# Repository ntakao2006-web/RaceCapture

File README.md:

# EcoLogger — 自作の車載データロガー

サーキット走行とエコラン大会で使う、自作の車載データロガーのリポジトリです。
走行中の値（回転数・車速・水温・油温・油圧・G・位置・ラップ）を記録し、車載画面に出し、LTEでピットへ送り、走行映像に計器を焼き込んで録画します。

## いまの姿（2026-11）

| | 中身 | 状態 |
|---|---|---|
| **Ver.2（本番機）** | Arduino UNO Q（Linux＋STM32）＋自作シールド＋UPS基板。車載画面（DASH）、LTE、焼き込み録画つき | 2026-11-08のSUGO 120分耐久を走った形 |
| Ver.1 | ESP32-S3の自作基板。RaceCaptureのアプリにつないで使う | 保険機として据え置き（機能の追加は凍結） |
| カート用 試作0号 | 画面つきの一体型（ESP32-S3） | 2026-11-29の走行に向けて準備中 |

もともとは「RaceCaptureのロガー端末だけを自作のハードウェアに置き換える」計画として始まりました（Ver.1）。
リポジトリ名と`ARCHITECTURE.md`の1〜3章はその頃のままです。

## 読む人ごとの入口

### 使う人（係・ドライバー）

- 当日の手順書（A4で印刷）：[`docs/manual/sugo_day_manual_20261108.html`](docs/manual/sugo_day_manual_20261108.html)（サーキット）、[`docs/manual/ecorun_day_manual_20261024.html`](docs/manual/ecorun_day_manual_20261024.html)（エコラン）
- 困ったとき：[`docs/manual/ecologger_troubleshooting.html`](docs/manual/ecologger_troubleshooting.html)
- PCの操作メニュー：`tools/ecologger_menu/`（デスクトップの「EcoLogger Ver.2」）
- 走行ログ・動画の回収：`tools/video_collect/Collect-Video.cmd`

### チーム

- ハードウェアとソフトウェアの構成図：[`v2_hardware_overview.html`](v2_hardware_overview.html)
- 仕様書（誰に・どの場面で・何をできるようにするか）：[`SPEC.md`](SPEC.md)

### 開発者

- **[`ARCHITECTURE.md`](ARCHITECTURE.md)** — 現在地とロードマップ（このリポジトリの一次情報源）
- 作業の分解：直下の`task_*_breakdown.md`（一覧は`ARCHITECTURE.md` 5章の冒頭「タスクの置き場所」）
- 資料1本ごとの案内：[`docs/README.md`](docs/README.md)、道具ごとの案内：[`tools/README.md`](tools/README.md)
- 各フォルダーの`README.md`

## フォルダー

| 場所 | 中身 |
|---|---|
| `RaceCapture-UNOQ/` | Ver.2のLinux側（車載画面DASH・見守り役など） |
| `EcoCapture-Web/` | Ver.2の上で動くEcoCapture（設定・ログ管理・LTE送信） |
| `tools/` | PCで使う道具（操作メニュー・回収・解析・動画）と、本体の録画のソフト`tools/unoq_overlay_enc/` |
| `tools/dev/` | 開発・調べもの用の道具 |
| `firmware/` | Ver.1のファームウェア（PlatformIO / ESP-IDF） |
| `android-logger/` | スマホのアプリ（エコランの車載画面） |
| `circuit/` | 回路・基板（KiCad） |
| `docs/design/` | 仕様・設計 |
| `docs/manual/` | 手順書 |
| `docs/research/` | 調査 |
| `docs/share/` | 人に渡したメモと、その回答 |
| `ecorun/` | エコランチームの用事（記録表） |
| `outputs/` | 確かめの記録（日付つき） |
| `archive/` | 閉じた系統の資料（ダッシュカム・通話など） |

走行ログ（`drive_logs/`）は位置情報を含むため、リポジトリには入れていません。

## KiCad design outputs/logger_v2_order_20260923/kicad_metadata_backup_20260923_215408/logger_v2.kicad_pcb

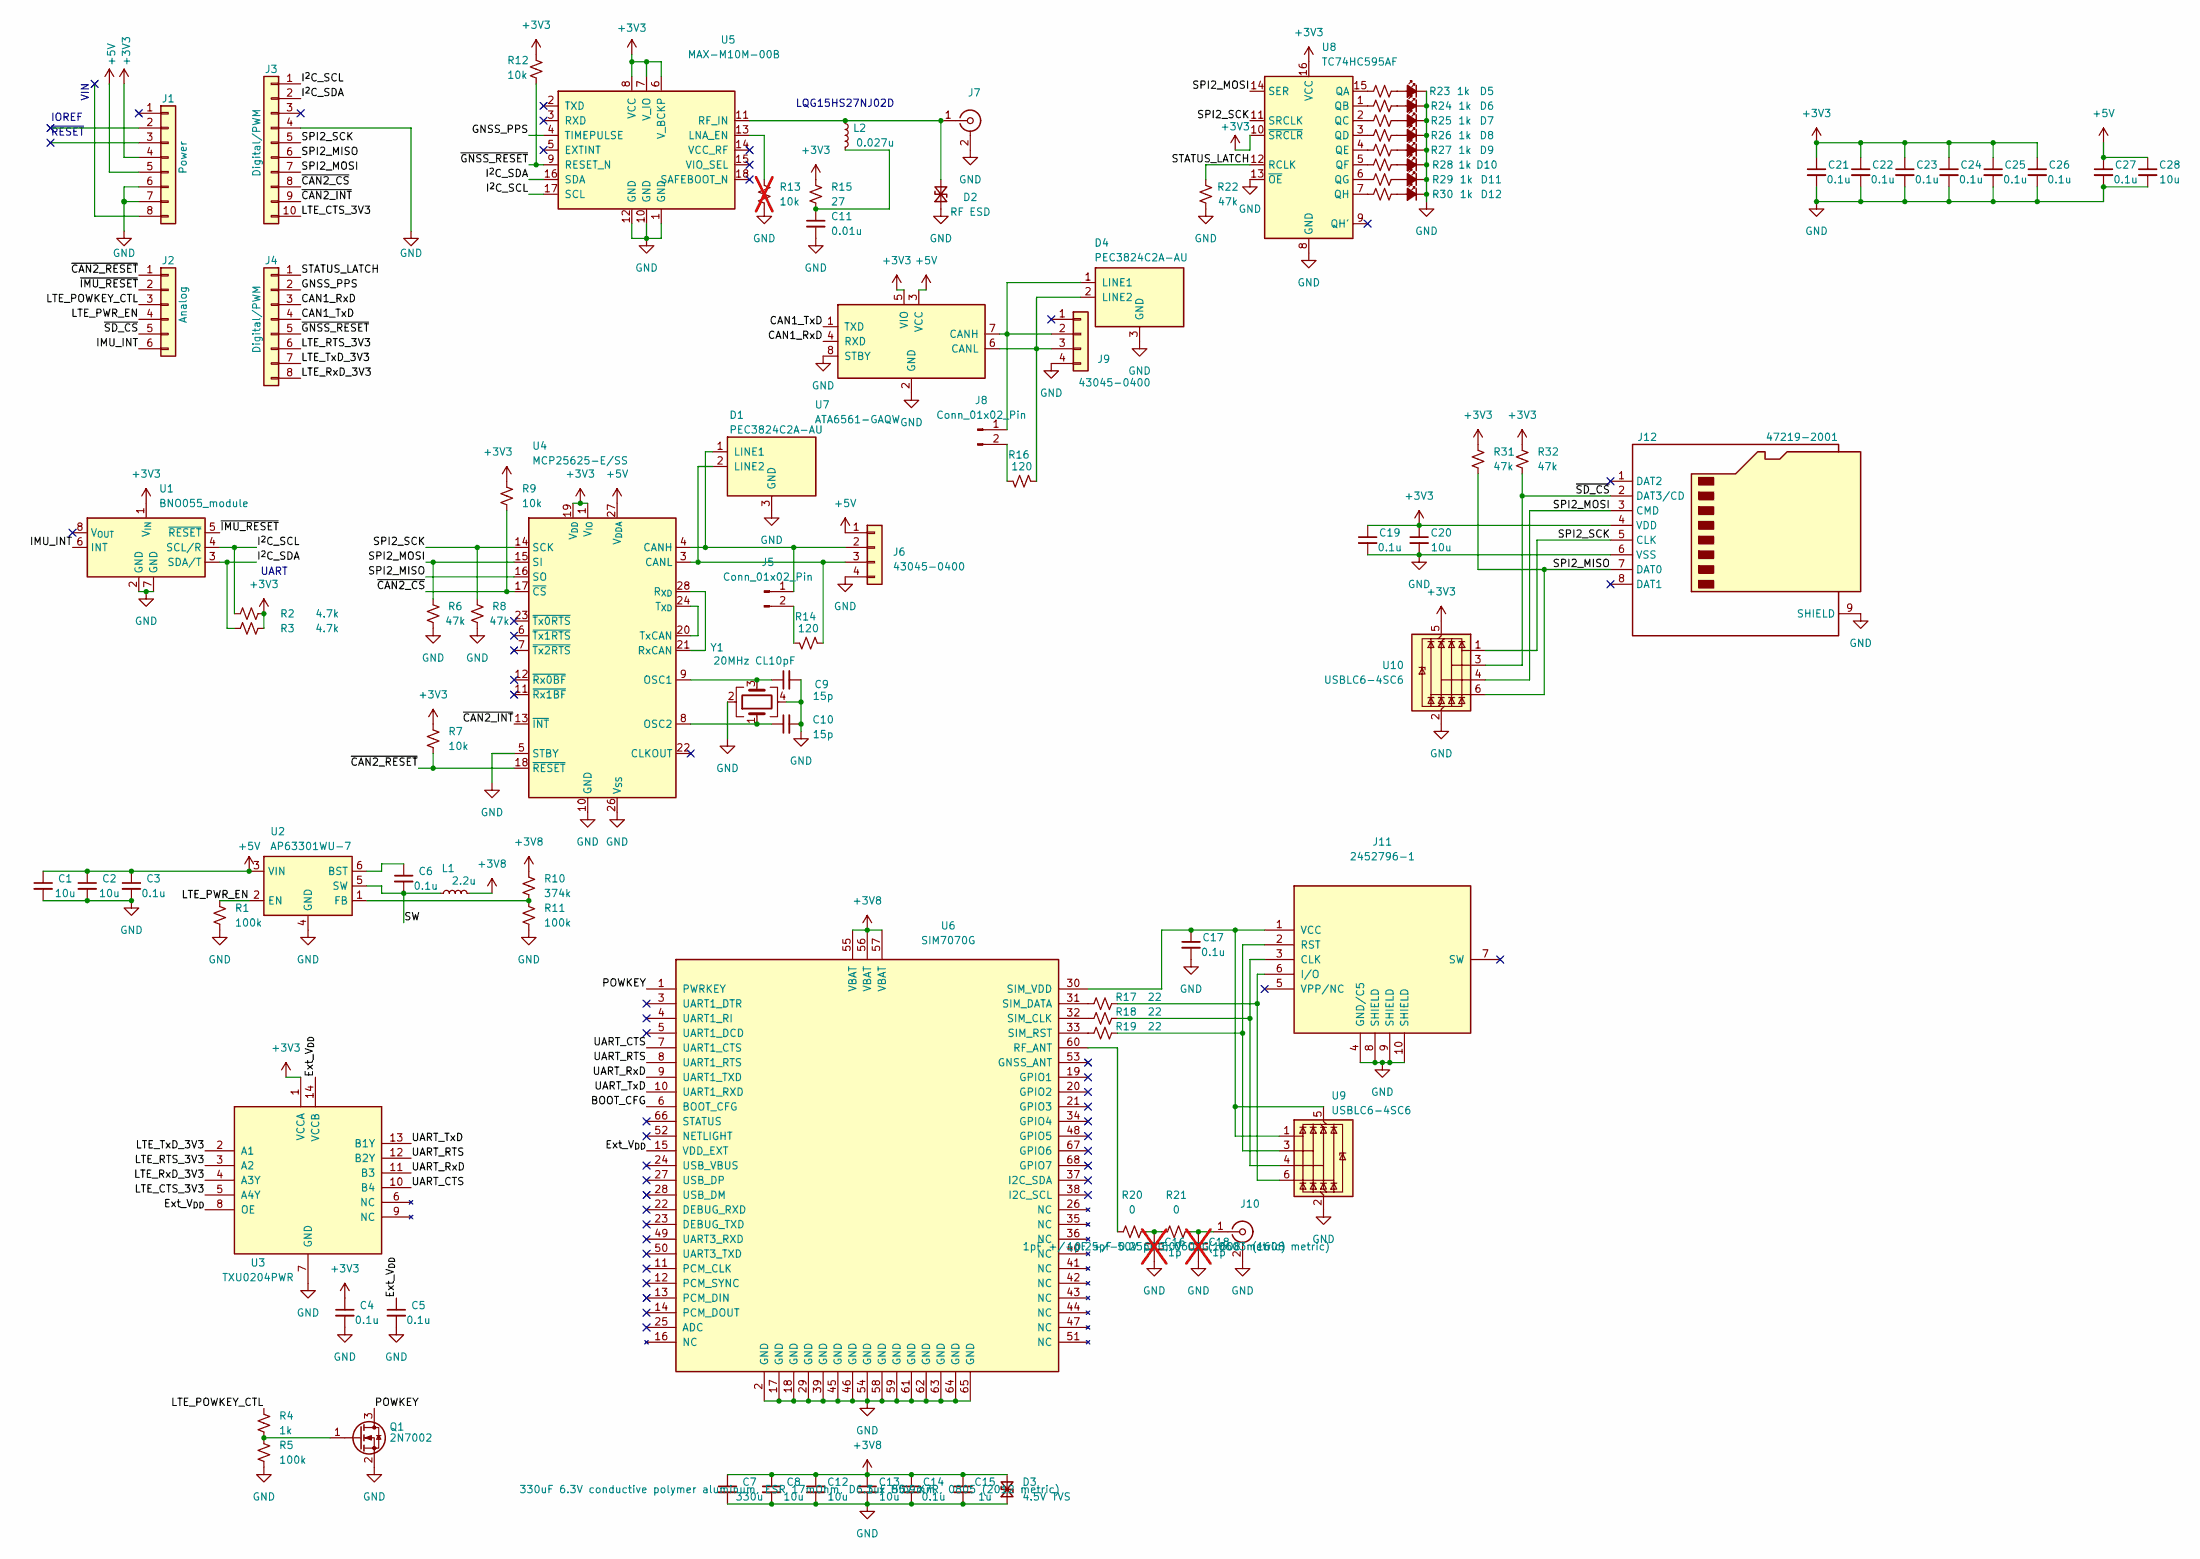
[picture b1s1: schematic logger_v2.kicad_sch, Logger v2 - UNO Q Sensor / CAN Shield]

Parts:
C1, C2, C8, C12, C13, C28: 10u; C_0805_2012Metric; MPN GRM21BR71A106KE51; LCSC C15850
C3, C4, C5, C6, C14, C17, C19, C21, C22, C23, C24, C25, C26, C27: 0.1u; C_0603_1608Metric; MPN GRM188R72A104KA35D; LCSC C14663
C7: 330u; CP_Elec_6.3x5.9; MPN 6SVPC330M
C9, C10: 15p; C_0603_1608Metric; MPN CC0603N150J500; LCSC C1647
C11: 0.01u; C_0603_1608Metric; MPN GRM188B11H103KA01; LCSC C14663
C15: 1u; C_0805_2012Metric; MPN C2012X7R1H105KT000N
C16, C18: 1p; C_0603_1608Metric; MPN CC0603CRNPO9BN1R0; not fitted
C20: 10u; C_0805_2012Metric; MPN C2012X7R1H105KT000N
D1, D4: PEC3824C2A-AU; SOT-23; MPN PEC3824C2A-AU_R1_000A1; LCSC C14486
D2: RF ESD; D_SOD-882; MPN PESD5V0F1BL-Q; LCSC C45961
D3: 4.5V TVS; Prisemi_DFN1006_2L
D5, D6, D7, D8, D9, D10, D11, D12: GREEN 0805; LED_0805_2012Metric_ShieldSilk; MPN OSG80805C1C; LCSC C2297
J1: Power; PinHeader_1x08_P2.54mm_Vertical; MPN FH105-1x8SG/RH
J2: Analog; PinHeader_1x06_P2.54mm_Vertical; MPN FH105-1x6SG/RH
J3: Digital/PWM; PinHeader_1x10_P2.54mm_Vertical; MPN FH105-1x10SG
J4: Digital/PWM; PinHeader_1x08_P2.54mm_Vertical; MPN FH105-1x8SG/RH
J5, J8: Conn_01x02_Pin; PinHeader_1x02_P2.54mm_Vertical
J6, J9: 43045-0400; Molex_Micro-Fit_3.0_43045-0400_2x02_P3.00mm_Horizontal; MPN 43045-0400
J7, J10: S-037-TGG; SMA_S-037-TGG_Horizontal; MPN S-037-TGG
J11: 2452796-1; nanoSIM_TE_2452796-1_Hinge; MPN 2452796-1
J12: 47219-2001; Molex_47219-2001; MPN 47219-2001
L1: 2.2u; L_Murata_DFE252012P; MPN DFE252012P-2R2M=P2
L2: 0.027u; L_0603_1608Metric; MPN LQW18AN27NJ00D
Q1: 2N7002; SOT-23; MPN 2N7002
R1, R5, R11: 100k; R_0603_1608Metric; MPN RK73B1JTTD103J; LCSC C25804
R2, R3: 4.7k; R_0603_1608Metric; MPN RK73B1JTTD472J; LCSC C23162
R4: 1k; R_0603_1608Metric; MPN RK73B1JTTD103J; LCSC C25804
R6, R8, R22: 47k; R_0603_1608Metric; MPN RC0603J47K; LCSC C25819
R7, R9, R12: 10k; R_0603_1608Metric; MPN RK73B1JTTD103J; LCSC C25804
R10: 374k; R_0603_1608Metric; MPN RK73B1JTTD103J; LCSC C25804
R13: 10k; R_0603_1608Metric; MPN RK73B1JTTD103J; LCSC C25804; not fitted
R14, R16: 120; R_0603_1608Metric; MPN RC0603J120R; LCSC C22787
R15: 27; R_2512_6332Metric; MPN CRCW251227R0JNEG; LCSC C25478
R17, R18, R19: 22; R_0603_1608Metric; MPN RK73B1JTTD103J; LCSC C25804
R20, R21: 0; R_0603_1608Metric; MPN RK73B1JTTD103J; LCSC C25804
R23, R24, R25, R26, R27, R28, R29, R30: 1k; R_0603_1608Metric; MPN RK73B1JTTD102J; LCSC C23228
R31, R32: 47k; R_0603_1608Metric; MPN RK73B1JTTD103J; LCSC C25804
U1: BNO055_module; AE_BNO055_BO_ShieldSilk; MPN AE-BNO055-BO
U2: AP63301WU-7; Diodes_TSOT26; MPN AP63301WU-7
U3: TXU0204PWR; TSSOP-14_4.4x5mm_P0.65mm; MPN TXU0204PWR
U4: MCP25625-E/SS; SSOP-28_5.3x10.2mm_P0.65mm; MPN MCP25625T-E/SS; LCSC C184944
U5: MAX-M10M-00B; MAX_M10M_00B_LCC18; MPN MAX-M10M-00B; LCSC C5119087
U6: SIM7070G; SIMCom_SIM7070G_LCC68_24x24mm_P1mm; MPN SIM7070G
U7: ATA6561-GAQW; SOIC-8_3.9x4.9mm_P1.27mm; MPN ATA6561-GAQW-N; LCSC C2929602
U8: TC74HC595AF; Toshiba_SOP16_P300_1.27A; MPN TC74HC595AF; LCSC C5947
U9, U10: USBLC6-4SC6; SOT-23-6; MPN USBLC6-4SC6
Y1: 20MHz CL10pF; Crystal_SMD_3225-4Pin_3.2x2.5mm; MPN 20M10PB/XT324-10/80; LCSC C18213008

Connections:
+3V3: C4.1, C19.1, C20.1, C21.1, C22.1, C23.1, C24.1, C25.1, C26.1, J1.4, J12.4 (VDD), R2.2, R3.2, R7.1, R9.1, R12.1, R15.1, R31.1, R32.1, U1.1 (V_{IN}), U3.1 (VCCA), U4.1 (V_{IO}), U4.19 (V_{DD}), U5.6 (V_BCKP), U5.7 (V_IO), U5.8 (VCC), U7.5 (VIO), U8.10 (~SRCLR), U8.16 (VCC), U10.5 (VBUS)
+3V8: C7.1, C8.1, C12.1, C13.1, C14.1, C15.1, D3.2 (A2), L1.2, R10.1, U6.55 (VBAT), U6.56 (VBAT), U6.57 (VBAT)
+5V: C1.1, C2.1, C3.1, C27.1, C28.1, J1.5, J6.1, U2.3 (VIN), U4.27 (V_{DDA}), U7.3 (VCC)
/BOOT_CFG: U6.6 (BOOT_CFG)
/CAN1_RxD: J4.3, U7.4 (RXD)
/CAN1_TxD: J4.4, U7.1 (TXD)
/Ext_V_{DD}: C5.1, U3.8 (OE), U3.14 (VCCB), U6.15 (VDD_EXT)
/GNSS_PPS: J4.2, U5.4 (TIMEPULSE)
/IMU_INT: J2.6, U1.6 (INT)
/I^{2}C_SCL: J3.1, R2.1, U1.4 (SCL/R), U5.17 (SCL)
/I^{2}C_SDA: J3.2, R3.1, U1.3 (SDA/T), U5.16 (SDA)
/LTE_CTS_3V3: J3.10, U3.5 (A4Y)
/LTE_POWKEY_CTL: J2.3, R4.1
/LTE_PWR_EN: J2.4, R1.1, U2.2 (EN)
/LTE_RTS_3V3: J4.6, U3.3 (A2)
/LTE_RxD_3V3: J4.8, U3.4 (A3Y)
/LTE_TxD_3V3: J4.7, U3.2 (A1)
/POWKEY: Q1.3 (D), U6.1 (PWRKEY)
/SPI2_MISO: J3.6, J12.7 (DAT0), R31.2, U4.16 (SO), U10.6 (I/O4)
/SPI2_MOSI: J3.7, J12.3 (CMD), R6.1, U4.15 (SI), U8.14 (SER), U10.4 (I/O3)
/SPI2_SCK: J3.5, J12.5 (CLK), R8.1, U4.14 (SCK), U8.11 (SRCLK), U10.1 (I/O1)
/STATUS_LATCH: J4.1, R22.1, U8.12 (RCLK)
/SW: C6.2, L1.1, U2.5 (SW)
/UART_CTS: U3.10 (B4), U6.7 (UART1_CTS)
/UART_RTS: U3.12 (B2Y), U6.8 (UART1_RTS)
/UART_RxD: U3.11 (B3), U6.9 (UART1_TXD)
/UART_TxD: U3.13 (B1Y), U6.10 (UART1_RXD)
/~CAN2_CS: J3.8, R9.2, U4.17 (~CS)
/~CAN2_INT: J3.9, U4.13 (~INT)
/~CAN2_RESET: J2.1, R7.2, U4.18 (~RESET)
/~GNSS_RESET: J4.5, R12.2, U5.9 (RESET_N)
/~IMU_RESET: J2.2, U1.5 (~RESET)
/~SD_CS: J2.5, J12.2 (DAT3/CD), R32.2, U10.3 (I/O2)
GND: C1.2, C2.2, C3.2, C4.2, C5.2, C7.2, C8.2, C9.2, C10.2, C11.2, C12.2, C13.2, C14.2, C15.2, C16.2, C17.2, C18.2, C19.2, C20.2, C21.2, C22.2, C23.2, C24.2, C25.2, C26.2, C27.2, C28.2, D1.3 (GND), D2.1 (A1), D3.1 (A1), D4.3 (GND), D5.1 (K), D6.1 (K), D7.1 (K), D8.1 (K), D9.1 (K), D10.1 (K), D11.1 (K), D12.1 (K), J1.6, J1.7, J3.4, J6.4, J7.2 (Ext), J9.4, J10.2 (Ext), J11.4 (GND/C5), J11.8 (SHIELD), J11.9 (SHIELD), J11.10 (SHIELD), J12.6 (VSS), J12.9 (SHIELD), Q1.2 (S), R1.2, R5.2, R6.2, R8.2, R11.2, R13.2, R22.2, U1.2 (GND), U1.7 (GND), U2.4 (GND), U3.7 (GND), U4.5 (STBY), U4.10 (GND), U4.26 (V_{SS}), U5.1 (GND), U5.10 (GND), U5.12 (GND), U6.2 (GND), U6.17 (GND), U6.18 (GND), U6.29 (GND), U6.39 (GND), U6.45 (GND), U6.46 (GND), U6.54 (GND), U6.58 (GND), U6.59 (GND)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
unnamed: C11.1, L2.2, R15.2
unnamed: C16.1, R20.2, R21.1
unnamed: D1.1 (LINE1), J5.1, J6.2, U4.4 (CANH)
unnamed: D1.2 (LINE2), J6.3, R14.1, U4.3 (CANL)
unnamed: D2.2 (A2), J7.1 (In), L2.1, U5.11 (RF_IN)
unnamed: D4.1 (LINE1), J8.1, J9.2, U7.7 (CANH)
unnamed: D4.2 (LINE2), J9.3, R16.1, U7.6 (CANL)
unnamed: D5.2 (A), R23.2
unnamed: D6.2 (A), R24.2
unnamed: D7.2 (A), R25.2
unnamed: D8.2 (A), R26.2
unnamed: D9.2 (A), R27.2
unnamed: D10.2 (A), R28.2
unnamed: D11.2 (A), R29.2
unnamed: D12.2 (A), R30.2
unnamed: J5.2, R14.2
unnamed: J8.2, R16.2
unnamed: C18.1, J10.1 (In), R21.2
unnamed: J11.3 (CLK), R18.2, U9.4 (I/O3)
unnamed: J11.6 (I/O), R17.2, U9.6 (I/O4)
unnamed: J11.2 (RST), R19.2, U9.3 (I/O2)
unnamed: C17.1, J11.1 (VCC), U6.30 (SIM_VDD), U9.1 (I/O1), U9.5 (VBUS)
unnamed: Q1.1 (G), R4.2, R5.1
unnamed: C6.1, U2.6 (BST)
unnamed: R10.2, R11.1, U2.1 (FB)
unnamed: C9.1, U4.9 (OSC1), Y1.3
unnamed: C10.1, U4.8 (OSC2), Y1.1
unnamed: U4.21 (RxCAN), U4.28 (R_{XD})
unnamed: U4.20 (TxCAN), U4.24 (T_{XD})
unnamed: R13.1, U5.13 (LNA_EN)
unnamed: R20.1, U6.60 (RF_ANT)
unnamed: R18.1, U6.32 (SIM_CLK)
unnamed: R17.1, U6.31 (SIM_DATA)
unnamed: R19.1, U6.33 (SIM_RST)
unnamed: R23.1, U8.15 (QA)
unnamed: R24.1, U8.1 (QB)
unnamed: R25.1, U8.2 (QC)
unnamed: R26.1, U8.3 (QD)
unnamed: R27.1, U8.4 (QE)
unnamed: R28.1, U8.5 (QF)
unnamed: R29.1, U8.6 (QG)
unnamed: R30.1, U8.7 (QH)

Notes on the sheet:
UART
~{RESET}
LQG15HS27NJ02D
VIN
IOREF

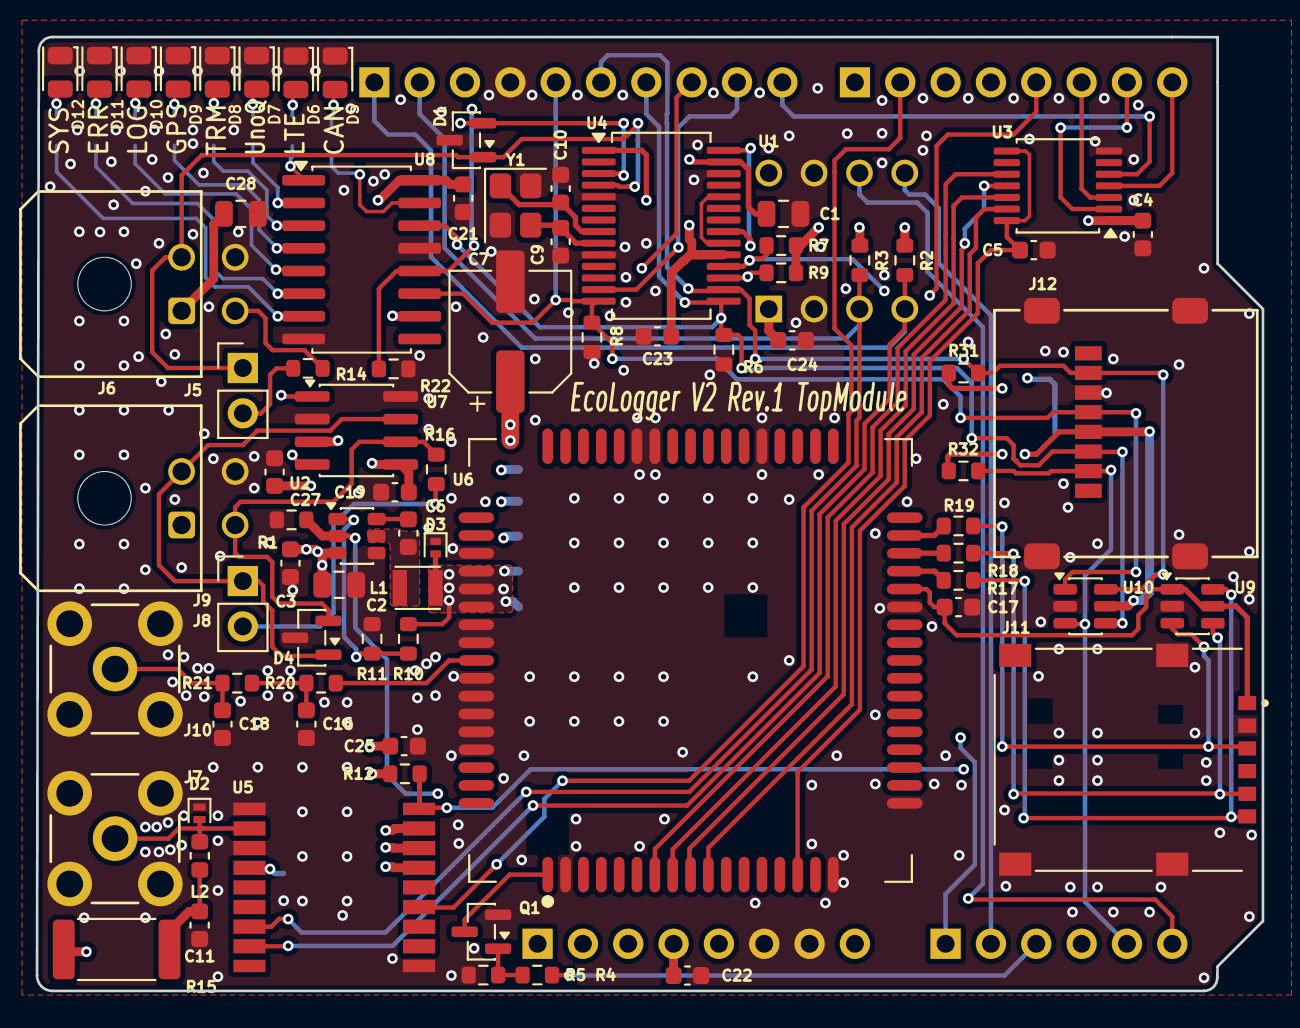
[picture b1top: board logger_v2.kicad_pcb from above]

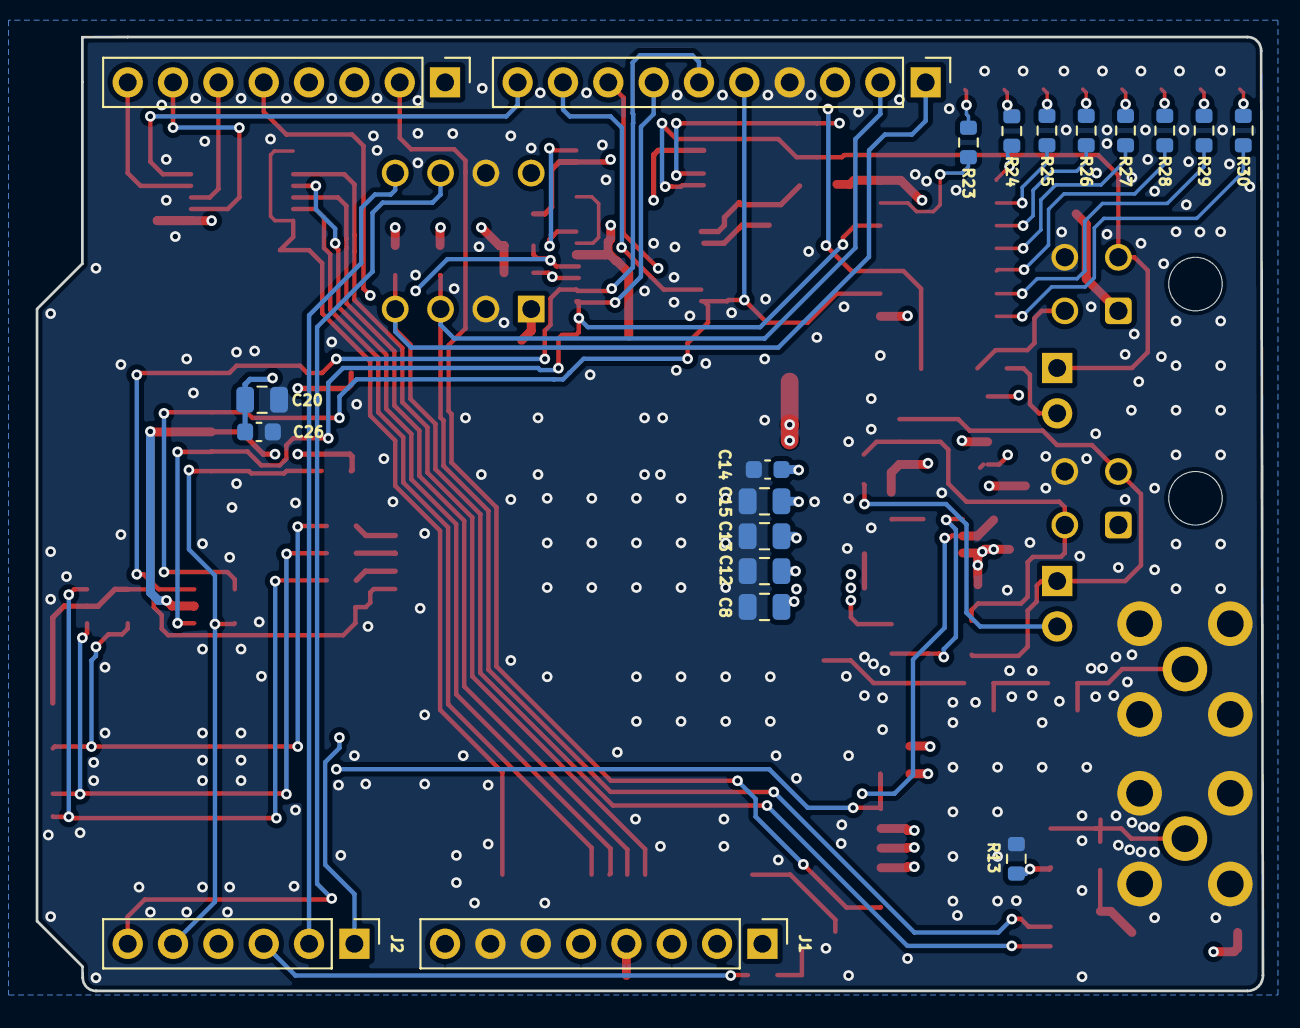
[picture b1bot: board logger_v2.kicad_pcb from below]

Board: 4 copper layers, 68.7 x 53.4 mm, 98 parts (20 on the bottom side), 75 nets.

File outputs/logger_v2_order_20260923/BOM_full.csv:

"状態","実装位置","品目","サイズ","メーカー品番","販売店","販売店品番","必要数","予備候補数","購入推奨数","選定根拠","製品URL"
"在庫表示あり","C1 C2 C8 C12 C13 C20 C28","10µF ±10% X7R 10V","0805 / 2012","CL21B106KPQNFNE","DigiKey","1276-2934-1-ND","7","3","10","旧445-6857-1-NDが注文画面で入荷待ちのため差替え。Samsung製10µF±10%・10V・X7R、2.00×1.25mm、高さ最大1.40mm。同じ0805ランドに実装可能。DigiKey製品ページの直販在庫65,218個、CT10個284円（税別）表示を2026-09-23確認。実装7＋予備3。C20は現行Value=10u。","https://www.digikey.jp/en/products/detail/samsung-electro-me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"
"在庫表示あり","C3 C4 C5 C6 C14 C17 C19 C21 C22 C23 C24 C25 C26 C27","100nF ±10% X7R 100V","0603 / 1608","GRM188R72A104KA35D","DigiKey","490-3285-1-ND","14","11","25","現行MPNを維持。C21～C27も現行Value=0.1u。","https://www.digikey.jp/en/products/detail/murata-electronics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"
"在庫表示あり","C7","330µF 6.3V ポリマー","φ6.3 × H5.9mm","6SVPC330M","DigiKey","P16611CT-ND","1","1","2","指定品維持。ESR17mΩ、極性あり。","https://www.digikey.jp/en/products/detail/panasonic-industry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"
"在庫表示あり","C9 C10","15pF ±5% C0G 50V","0603 / 1608","CC0603JRNPO9BN150","DigiKey","311-1060-1-ND","2","8","10","Value=15pを採用。古いSpecificationの18pF/CL12pFは不採用。 少量価格の段差も考慮して10個。","https://www.digikey.jp/en/products/detail/yageo/CC0603JRNPO9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"
"在庫表示あり","C11","10nF ±10% X7R 100V","0603 / 1608","GRM188R72A103KA01D","DigiKey","490-GRM188R72A103KA01DCT-ND","1","9","10","現行Value=0.01u。耐圧は元の50V以上。 少量価格の段差も考慮して10個。","https://www.digikey.jp/en/products/detail/murata-electronics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"
"在庫表示あり","C15","1µF ±10% X7R 50V","0805 / 2012","C2012X7R1H105K085AC","DigiKey","445-14539-1-ND","1","2","3","同サイズ・同容量・同耐圧。高さ最大1.0mm。新規設計非推奨品だが在庫表示あり。","https://www.digikey.jp/en/products/detail/tdk-corporation/C2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"
"在庫表示あり","D1 D4","CAN用 双方向2線 TVS 24V","SOT-23-3","ESDCAN24-2BLY","DigiKey","497-13262-1-ND","2","2","4","PEC3824C2A-AUの代替。1/2=CAN、3=GND。24V、Vbr最低27V、容量最大30pF。クランプ特性は元品と完全同一ではない。","https://www.digikey.jp/en/products/detail/stmicroelectronics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"
"在庫表示あり","D5 D6 D7 D8 D9 D10 D11 D12","緑LED 571nm / Vf約2V","0805 / 2012","LTST-C170KGKT","DigiKey","160-1414-1-ND","8","4","12","同0805、1=カソード、2=アノード。元品と発光色・明るさに差あり。","https://www.digikey.jp/en/products/detail/liteon/LTST-C170KG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"
"在庫表示あり","J6 J9","Micro-Fit 3.0 基板側4極","2×2 / 3.0mm 横向きTHT","43045-0400","DigiKey","WM1814-ND","2","0","2","43045-0400と同じ品番の表記違い。指定どおり2個だけ。ケーブル側・圧着端子は含めない。","https://www.digikey.jp/en/products/detail/molex/0430450400/252527"
"在庫表示あり","J11","nanoSIM ヒンジ式ソケット","TE専用フットプリント","2452796-1","DigiKey","343-2452796-1CT-ND","1","1","2","SDとは別部品。現行指定品維持。マーケットプレイス品ではなくDigiKey直販CTを指定。","https://www.digikey.jp/en/products/detail/te-connectivity-li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"
"在庫表示あり","L1","2.2µH ±20% 電源インダクタ","2.5×2.0×1.2mm","DFE252012F-2R2M=P2","DigiKey","490-13055-1-ND","1","2","3","旧490-10649-1-NDがユーザーのカートで規制表示のためFシリーズへ差替え。2.2µH±20%、外形・高さ・推奨ランド（内側1.2/外側2.8/幅2.0mm）は元品と一致。Irms2.3A / Isat3.3A / DCR82mΩ最大（元2.2A/3.0A/84mΩ）。DigiKey直販190,191個、1個税別42円の表示を2026-09-23確認。3個＝実装1＋予備2。ユーザーカートでの規制解除は未確認。","https://www.digikey.jp/en/products/detail/murata-electronics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"
"在庫表示あり","L2","27nH RF巻線インダクタ","0603 / 1608","LQW18AN27NJ00D","DigiKey","490-1174-1-ND","1","2","3","指定品維持。440mA、SRF3.7GHz以上。一般電源用インダクタには置換しない。","https://www.digikey.jp/en/products/detail/murata-electronics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"
"在庫表示あり","Q1","Nch MOSFET 60V","SOT-23","2N7002ET1G","DigiKey","2N7002ET1GOSCT-ND","1","2","3","2N7002相当。1=G、2=S、3=Dで基板と一致。","https://www.digikey.jp/en/products/detail/onsemi/2N7002ET1G/1792136"
"在庫表示あり","R1 R5 R11","100kΩ ±0.1% 0.1W","0603 / 1608","CRT0603-BY-1003ELF","DigiKey","CRT0603-BY-1003ELFCT-ND","3","7","10","0603・100kΩ・0.1%・0.1W。R11の帰還精度を優先し同一品へ統一。","https://www.digikey.jp/en/products/detail/bourns-inc/CRT0603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"
"在庫表示あり","R4 R23 R24 R25 R26 R27 R28 R29 R30","1kΩ ±1% 0.1W","0603 / 1608","RC0603FR-071KL","DigiKey","311-1.00KHRCT-ND","9","6","15","Value基準。古いMPNに10kΩ表記が残る箇所あり。","https://www.digikey.jp/en/products/detail/yageo/RC0603FR-071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"
"在庫表示あり","R6 R8 R22 R31 R32","47kΩ ±1% 0.1W","0603 / 1608","RC0603FR-0747KL","DigiKey","311-47.0KHRCT-ND","5","5","10","同サイズの1%品。","https://www.digikey.jp/en/products/detail/yageo/RC0603FR-074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"
"在庫表示あり","R10","374kΩ ±1% 0.1W","0603 / 1608","RC0603FR-07374KL","DigiKey","311-374KHRCT-ND","1","9","10","電源帰還上側。Value=374kを採用。 少量価格の段差も考慮して10個。","https://www.digikey.jp/en/products/detail/yageo/RC0603FR-073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"
"在庫表示あり","R14 R16","120Ω ±1% 0.1W","0603 / 1608","RC0603FR-07120RL","DigiKey","311-120HRCT-ND","2","8","10","現行DNP=noのため含む。接続するCANバスの終端配置に従って実装する。 少量価格の段差も考慮して10個。","https://www.digikey.jp/en/products/detail/yageo/RC0603FR-071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"
"在庫表示あり","R17 R18 R19","22Ω ±1% 0.1W","0603 / 1608","CRCW060322R0FKEA","DigiKey","541-22.0HCT-ND","3","7","10","0603・22Ω・1%・0.1Wを維持。在庫表示のあるVishay品。","https://www.digikey.jp/en/products/detail/vishay-dale/CRCW06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"
"在庫表示あり","R20 R21","0Ω ジャンパ 0.1W","0603 / 1608","RC0603JR-070RL","DigiKey","311-0.0GRCT-ND","2","8","10","現行Value=0Ω。 少量価格の段差も考慮して10個。","https://www.digikey.jp/en/products/detail/yageo/RC0603JR-070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"
"在庫表示あり","R15","27Ω ±5% 1W","2512 / 6332","RMCF2512JT27R0","DigiKey","RMCF2512JT27R0CT-ND","1","2","3","2512・27Ω・5%・1Wを維持。同サイズのStackpole品へ置換。","https://www.digikey.jp/en/products/detail/stackpole-electron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"
"在庫表示あり","U2","3A 降圧DC/DC","TSOT26","AP63301WU-7","DigiKey","31-AP63301WU-7CT-ND","1","1","2","指定品維持。AP63300/固定電圧版と混同しない。","https://www.digikey.jp/en/products/detail/diodes-incorporate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"
"在庫表示あり","U3","4bit レベル変換","TSSOP-14 / P0.65","TXU0204PWR","DigiKey","296-TXU0204PWRCT-ND","1","1","2","指定品維持。PWパッケージ。","https://www.digikey.jp/en/products/detail/texas-instruments/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"
"在庫表示あり","U4","CANコントローラ＋トランシーバ","SSOP-28 / 幅5.3mm","MCP25625T-E/SS","DigiKey","MCP25625T-E/SSCT-ND","1","0","1","指定品維持。/SSパッケージ。高価なため予備なし。","https://www.digikey.jp/en/products/detail/microchip-technolo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"
"在庫表示あり","U6","LTE Cat-M/NB-IoTモジュール","LCC-68 / 24×24mm","SIM7070G","DigiKey","3781-SIM7070G-ND","1","0","1","指定の裸モジュール。開発ボードではない。高価なため予備なし。","https://www.digikey.jp/en/products/detail/simcom-wireless-so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"
"在庫表示あり","U7","CANトランシーバ","SOIC-8 / 幅3.9mm","ATA6561-GAQW-N","DigiKey","ATA6561-GAQW-NCT-ND","1","1","2","指定品維持。VDFN版を選ばない。","https://www.digikey.jp/en/products/detail/microchip-technolo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"
"在庫表示あり","U8","8bit シフトレジスタ","SOP-16 / 幅5.3mm","TC74HC595AF(EL,F)","DigiKey","264-TC74HC595AF(EL,F)CT-ND","1","1","2","指定AFのSOP16を維持。一般的な幅3.9mm SOICの74HC595は合わない。","https://www.digikey.jp/en/products/detail/toshiba-semiconduc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"
"在庫表示あり","U9 U10","4線ESD保護","SOT-23-6","USBLC6-4SC6Y","DigiKey","497-11883-1-ND","2","2","4","USBLC6-4SC6の車載グレード品。同じ4線・SOT23-6・ピン配置。2=GND、5=VBUS、1/3/4/6=I/O。","https://www.digikey.jp/en/products/detail/stmicroelectronics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"
"在庫表示あり","Y1","水晶 20MHz / CL10pF","3225 / 4端子","ABM8-20.000MHZ-10-B1U-T","DigiKey","535-14973-1-ND","1","1","2","同寸法3.2×2.5mm、CL10pF。1/3=水晶、2/4=GND。発振余裕は実機で確認。","https://www.digikey.jp/en/products/detail/abracon-llc/ABM8-2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"
"在庫表示あり：機能代替","D2","RF用 双方向TVS 5.3V / 0.35pF","SOD882 / 1.0×0.6mm","AQ3045-01ETG","DigiKey","F9321CT-ND","1","2","3","GNSSアンテナESD用の機能代替。SOD882・端子ピッチ0.65mm、現PCBの0.4×0.7mmパッドに端子が重なる。容量typ0.35/max0.5pF（元0.4/0.55）、双方向。VRWM5.3V（元5.5）、Vc最大12V@1A（元11V@1A）で全特性同一ではない。3A・ESD±30kV。DigiKey直販82,168個表示。RF/ESD実機試験未実施。","https://www.digikey.jp/en/products/detail/littelfuse-inc/AQ3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"
"在庫表示あり：機能代替","D3","LTE電源 双方向TVS 4.5V","CSP1006-2 / 1.0×0.6mm","CSPSBHC4V5LB-TP","DigiKey","353-CSPSBHC4V5LB-TPCT-ND","1","2","3","3.8V電源ESD用の機能代替。4.5V双方向、端子ピッチ0.65mm・長さ0.20～0.30/幅0.45～0.55mmで現PCBの0.4×0.6mmパッドに実装可能。Vc最大8.5V@50A/10.5V@100A（元12V@25A）、100A/900W。容量最大300pF、Tj上限125℃。元品のVhold最低4.6Vに対し本品は保証値記載なし、1Aクランプも保証値なし。全特性同一ではなく、実機サージ後復帰は未検証。DigiKey地域ページに10,002個表示。","https://www.digikey.jp/en/products/detail/mcc-micro-commerci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"

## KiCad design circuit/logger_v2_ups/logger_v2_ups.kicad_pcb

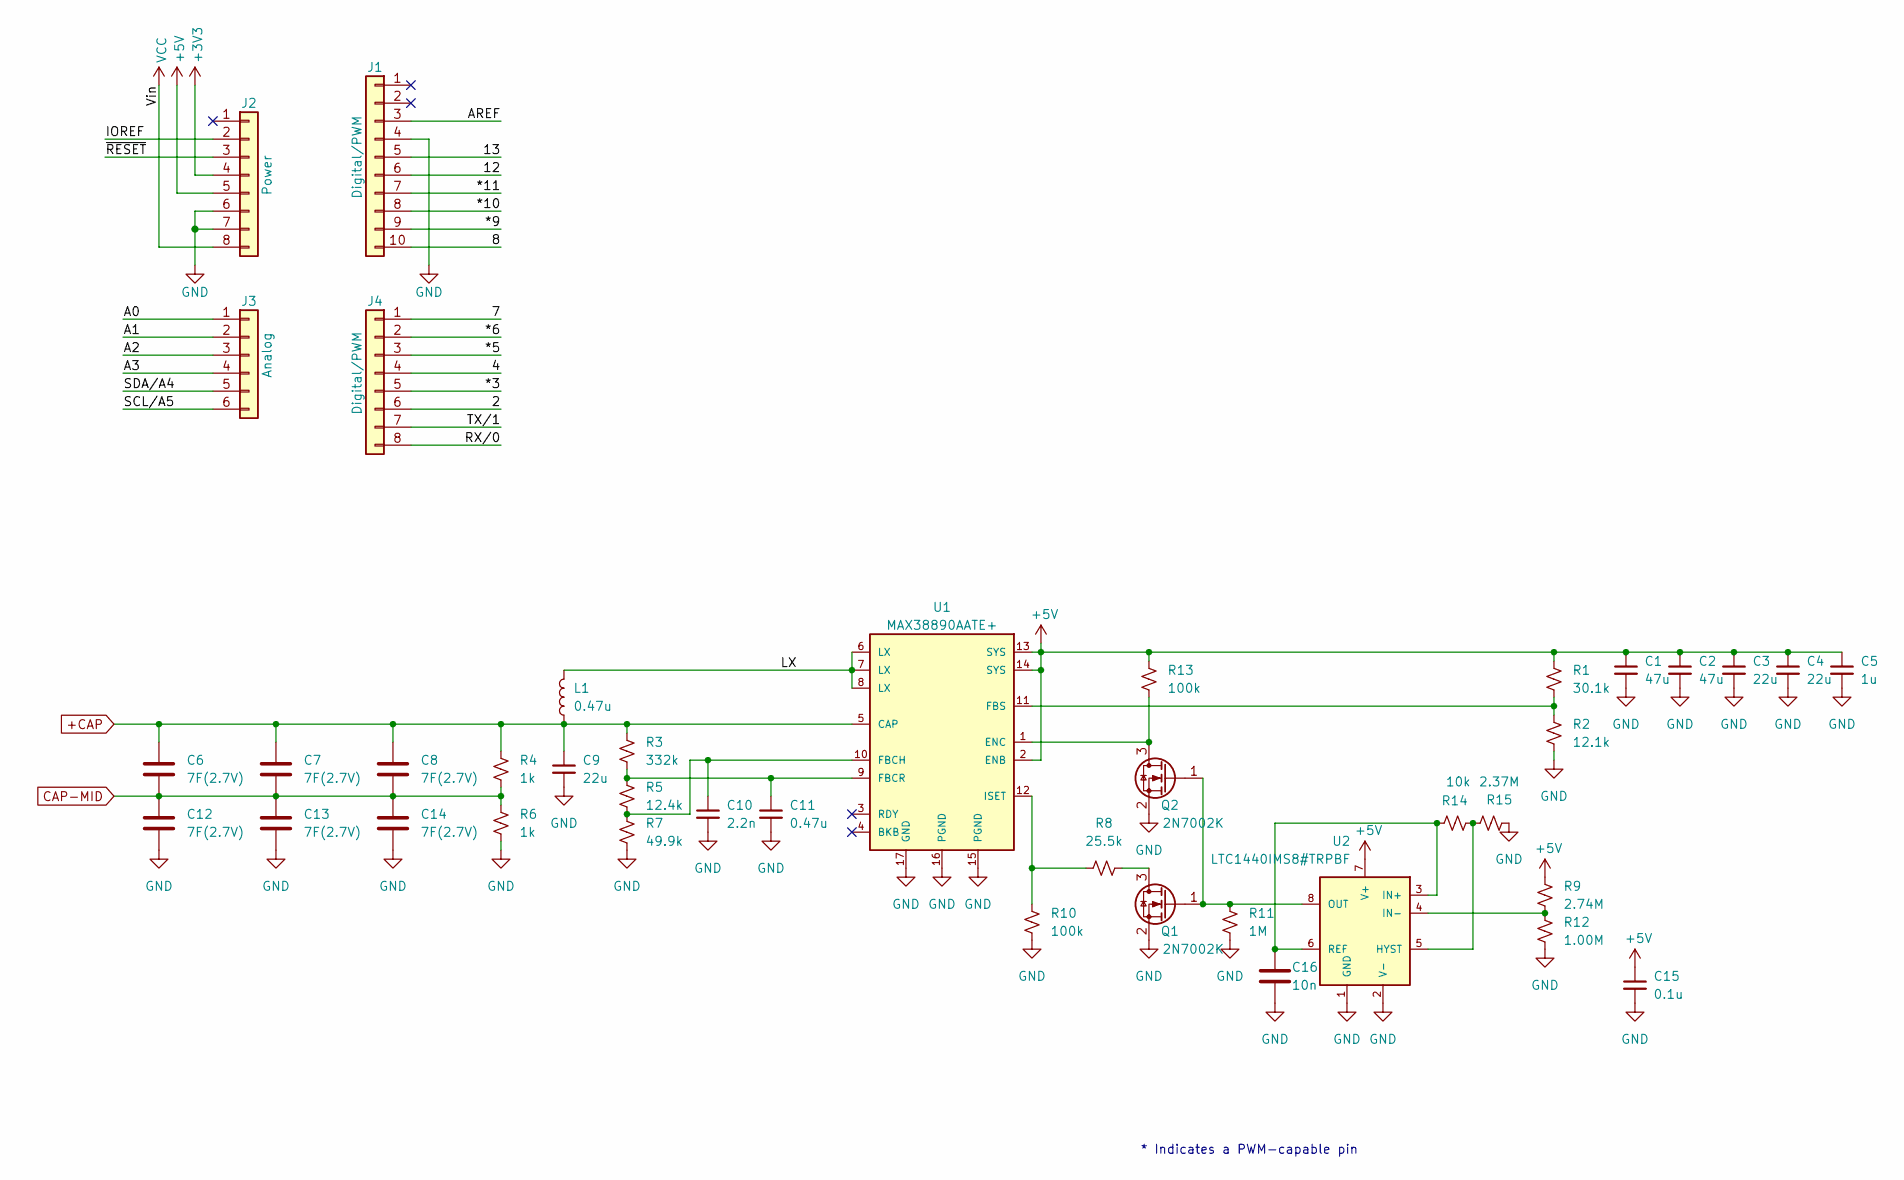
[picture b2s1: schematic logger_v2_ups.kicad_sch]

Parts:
C1, C2: 47u; CP_Elec_6.3x5.9; Rating 47uF 25V aluminum solid polymer; ESR 30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; MPN 25SVPF47M; DigiKey P16513CT-ND
C3, C4, C9: 22u; C_1206_3216Metric; Rating 22uF +/-20%; 16V; X7R MLCC; 3216 (1206)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; MPN EMK316BB7226ML-T; DigiKey 587-4319-1-ND
C5: 1u; C_0805_2012Metric; Rating 1uF 50V X7R +/-10% MLCC 0805; MPN C0805C105K5RACTU; DigiKey 399-C0805C105K5RACTUCT-ND
C6, C7, C8, C12, C13, C14: 7F(2.7V); Eaton_HVH1020-2R7705-R_D10_L20_P5_Horizontal; Rating 7F +/-20%; 2.7V; ESR DC max113mohm / 1k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; MPN HVH1020-2R7705-R; DigiKey 283-HVH1020-2R7705-R-ND
C10: 2.2n; C_0805_2012Metric; Rating 2.2nF 50V C0G +/-5% MLCC 0805; MPN C0805C222J5GACTU; DigiKey 399-C0805C222J5GACTUCT-ND
C11: 0.47u; C_0805_2012Metric; Rating 0.47uF 50V X7R +/-10% MLCC 0805; MPN C0805C474K5RACTU; DigiKey 399-C0805C474K5RACTUCT-ND
C15: 0.1u; C_0603_1608Metric; Rating 0.1uF; 50V; X7R MLCC; +/-10%; 0603 (160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; MPN C0603C104K5RACTU; DigiKey 399-C0603C104K5RACTUCT-ND
C16: 10n; C_0603_1608Metric; Rating 10nF; 50V; X7R MLCC; +/-10%; 0603 (1608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; MPN C0603C103K5RACTU; DigiKey 399-C0603C103K5RACTUCT-ND
J1: Digital/PWM; PinSocket_1x10_P2.54mm_Vertical; Rating 2.54mm THT female socket; 4.7A per cont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; MPN SSW-110-01-T-S; DigiKey 612-SSW-110-01-T-S-ND
J2: Power; PinSocket_1x08_P2.54mm_Vertical; Rating 2.54mm THT female socket; 4.7A per cont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; MPN SSW-108-01-T-S; DigiKey 612-SSW-108-01-T-S-ND
J3: Analog; PinSocket_1x06_P2.54mm_Vertical; Rating 2.54mm THT female socket; 4.7A per cont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; MPN SSW-106-01-T-S; DigiKey 612-SSW-106-01-T-S-ND
J4: Digital/PWM; PinSocket_1x08_P2.54mm_Vertical; Rating 2.54mm THT female socket; 4.7A per cont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; MPN SSW-108-01-T-S; DigiKey 612-SSW-108-01-T-S-ND
L1: 0.47u; L_Wuerth_HCI-1365; Rating 0.47uH +/-20%; Ir 30A; Isat10% 25A; Isa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; MPN 744355147; DigiKey 732-744355147CT-ND
Q1, Q2: 2N7002K; SOT-23; Rating N-channel MOSFET; 60V VDS; 380mA at VGS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; MPN 2N7002K-7-W; DigiKey 31-2N7002K-7-WCT-ND
R1: 30.1k; R_0805_2012Metric; Rating 0805; 30.1kOhm; +/-1%; 0.125W; MPN ERJ-6ENF3012V; DigiKey P30.1KCCT-ND
R2: 12.1k; R_0805_2012Metric; Rating 0805; 12.1kOhm; +/-1%; 0.125W; MPN RC0805FR-0712K1L; DigiKey 311-12.1KCRCT-ND
R3: 332k; R_0805_2012Metric; Rating 0805; 332kOhm; +/-1%; 0.125W; MPN RC0805FR-07332KL; DigiKey 311-332KCRCT-ND
R4, R6: 1k; R_0805_2012Metric; Rating 0805 0.125W +/-1%; 150V working voltage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; MPN RC0805FR-071KL; DigiKey 311-1.00KCRCT-ND
R5: 12.4k; R_0805_2012Metric; Rating 0805; 12.4kOhm; +/-1%; 0.125W; MPN RC0805FR-0712K4L; DigiKey 311-12.4KCRCT-ND
R7: 49.9k; R_0805_2012Metric; Rating 0805; 49.9kOhm; +/-1%; 0.125W; MPN RC0805FR-0749K9L; DigiKey 311-49.9KCRCT-ND
R8: 25.5k; R_0603_1608Metric; Rating 0603 (1608 metric); 0.1W; +/-1%; 75V ma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; MPN RC0603FR-0725K5L; DigiKey 311-25.5KHRCT-ND
R9: 2.74M; R_0603_1608Metric; Rating 0603; 2.74MOhm; +/-1%; 0.1W; MPN RC0603FR-072M74L; DigiKey 13-RC0603FR-072M74LCT-ND
R10, R13: 100k; R_0603_1608Metric; Rating 0603 (1608 metric); 0.1W; +/-1%; 75V ma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; MPN RC0603FR-07100KL; DigiKey 311-100KHRCT-ND
R11: 1M; R_0603_1608Metric; Rating 0603 (1608 metric); 0.1W; +/-1%; 75V ma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; MPN RC0603FR-071ML; DigiKey 311-1.00MHRCT-ND
R12: 1.00M; R_0603_1608Metric; Rating 0603 (1608 metric); 0.1W; +/-1%; 75V ma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; MPN RC0603FR-071ML; DigiKey 311-1.00MHRCT-ND
R14: 10k; R_0603_1608Metric; Rating 0603; 10kOhm; +/-1%; 0.1W; MPN ERJ-3EKF1002V; DigiKey P10.0KHCT-ND
R15: 2.37M; R_0603_1608Metric; Rating 0603; 2.37MOhm; +/-1%; 0.1W; MPN RC0603FR-072M37L; DigiKey 13-RC0603FR-072M37LCT-ND
U1: MAX38890AATE+; TQFN-16-1EP_3x3mm_P0.5mm_EP1.23x1.23mm; Rating VSYS 2.5..5.5V; peak inductor current 1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; MPN MAX38890AATE+; DigiKey 505-MAX38890AATE+-ND
U2: LTC1440IMS8#TRPBF; MSOP-8_3x3mm_P0.65mm; Rating Comparator with 1.182V reference; MSOP-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; MPN LTC1440IMS8#TRPBF; DigiKey LTC1440IMS8#TRPBFCT-ND

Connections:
+3V3: J2.4
+5V: C1.1, C2.1, C3.1, C4.1, C5.1, C15.1, J2.5, R1.1, R9.1, R13.1, U1.2 (ENB), U1.13 (SYS), U1.14 (SYS), U2.7 (V+)
+CAP: C6.1, C7.1, C8.1, C9.1, L1.2, R3.1, R4.1, U1.5 (CAP)
/2: J4.6
/4: J4.4
/7: J4.1
/8: J1.10
/12: J1.6
/13: J1.5
/*3: J4.5
/*5: J4.3
/*6: J4.2
/*9: J1.9
/*10: J1.8
/*11: J1.7
/A0: J3.1
/A1: J3.2
/A2: J3.3
/A3: J3.4
/AREF: J1.3
/IOREF: J2.2
/LX: L1.1, U1.6 (LX), U1.7 (LX), U1.8 (LX)
/RX/0: J4.8
/SCL/A5: J3.6
/SDA/A4: J3.5
/TX/1: J4.7
/~RESET: J2.3
CAP-MID: C6.2, C7.2, C8.2, C12.1, C13.1, C14.1, R4.2, R6.1
GND: C1.2, C2.2, C3.2, C4.2, C5.2, C9.2, C10.2, C11.2, C12.2, C13.2, C14.2, C15.2, C16.2, J1.4, J2.6, J2.7, Q1.2 (S), Q2.2 (S), R2.2, R6.2, R7.2, R10.2, R11.2, R12.2, R15.2, U1.15 (PGND), U1.16 (PGND), U1.17 (GND), U2.1 (GND), U2.2 (V-)
unnamed: Q1.3 (D), R8.2
unnamed: Q1.1 (G), Q2.1 (G), R11.1, U2.8 (OUT)
unnamed: Q2.3 (D), R13.2, U1.1 (ENC)
unnamed: C10.1, R5.2, R7.1, U1.10 (FBCH)
unnamed: C11.1, R3.2, R5.1, U1.9 (FBCR)
unnamed: R1.2, R2.1, U1.11 (FBS)
unnamed: R8.1, R10.1, U1.12 (ISET)
unnamed: R14.2, R15.1, U2.5 (HYST)
unnamed: C16.1, R14.1, U2.3 (IN+), U2.6 (REF)
unnamed: R9.2, R12.1, U2.4 (IN-)
VCC: J2.8

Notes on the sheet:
* Indicates a PWM-capable pin

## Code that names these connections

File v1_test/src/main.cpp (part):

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constexpr gpio_num_t LED_SER = GPIO_NUM_40;
constexpr gpio_num_t LED_CLK = GPIO_NUM_39;
constexpr gpio_num_t LED_LATCH = GPIO_NUM_45;
constexpr gpio_num_t SD_CLK = GPIO_NUM_11;
constexpr gpio_num_t SD_CMD = GPIO_NUM_10;
constexpr gpio_num_t SD_D0 = GPIO_NUM_12;
constexpr gpio_num_t SD_D1 = GPIO_NUM_13;
constexpr gpio_num_t SD_D2 = GPIO_NUM_14;
constexpr gpio_num_t SD_D3 = GPIO_NUM_21;
constexpr gpio_num_t GNSS_RX = GPIO_NUM_15;
constexpr gpio_num_t GNSS_TX = GPIO_NUM_16;
constexpr gpio_num_t GNSS_RESET_N = GPIO_NUM_9;
constexpr gpio_num_t GNSS_TIMEPULSE = GPIO_NUM_8;
constexpr gpio_num_t IMU_RESET_N = GPIO_NUM_7;
constexpr gpio_num_t IMU_I2C_SDA = GPIO_NUM_17;  // Module pin 3 SDA/T
constexpr gpio_num_t IMU_I2C_SCL = GPIO_NUM_18;  // Module pin 4 SCL/R
constexpr i2c_port_t IMU_I2C_PORT = I2C_NUM_0;
constexpr uint32_t IMU_I2C_HZ = 100000;
constexpr gpio_num_t CAN1_RX = GPIO_NUM_1;
constexpr gpio_num_t CAN1_TX = GPIO_NUM_2;
constexpr gpio_num_t CAN2_RESET = GPIO_NUM_4;
constexpr gpio_num_t CAN2_SCK = GPIO_NUM_39;
constexpr gpio_num_t CAN2_MOSI = GPIO_NUM_40;
constexpr gpio_num_t CAN2_MISO = GPIO_NUM_41;
constexpr gpio_num_t CAN2_CS = GPIO_NUM_42;
constexpr gpio_num_t OTG_VBUS_SENSE = GPIO_NUM_6;
constexpr gpio_num_t OTG_OC_N = GPIO_NUM_38;
constexpr gpio_num_t OTG_ROLE = GPIO_NUM_48;

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bool init_imu()
{
    gpio_config_t reset = {};
    reset.pin_bit_mask = 1ULL << IMU_RESET_N;
    reset.mode = GPIO_MODE_OUTPUT;
    ESP_ERROR_CHECK(gpio_config(&reset));
    gpio_set_level(IMU_RESET_N, 0);
    vTaskDelay(pdMS_TO_TICKS(20));

    i2c_config_t config = {};
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        return false;
    }

    gpio_set_level(IMU_RESET_N, 1);
    vTaskDelay(pdMS_TO_TICKS(800));

    diag.imu_sda_idle = gpio_get_level(IMU_I2C_SDA);
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        }
        ESP_LOGI(TAG, "health cpu=%luMHz temp=%.1fC max=%.1fC stress=%s OTG(vbus=%d role=%d oc_n=%d)",
                 static_cast<unsigned long>(diag.cpu_mhz), diag.temp_c, diag.max_temp_c,
                 stress_enabled ? "ON" : "OFF", gpio_get_level(OTG_VBUS_SENSE),
                 gpio_get_level(OTG_ROLE), gpio_get_level(OTG_OC_N));
        vTaskDelay(pdMS_TO_TICKS(5000));
    }
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             static_run_pass ? "PASS" : "FAIL", physical_low, physical_high);

    gpio_config_t reset = {};
    reset.pin_bit_mask = 1ULL << GNSS_RESET_N;
    reset.mode = GPIO_MODE_INPUT_OUTPUT_OD;
    ESP_ERROR_CHECK(gpio_config(&reset));
    gpio_set_level(GNSS_RESET_N, 0);
    vTaskDelay(pdMS_TO_TICKS(20));
    gpio_set_level(GNSS_TX, 0);
    esp_rom_delay_us(1000);
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    ESP_LOGI(TAG, "GNSS GPIO15 control drive/read while RESET_N Low: %s (low=%d high=%d)",
             control_pass ? "PASS" : "FAIL", control_low, control_high);
    ESP_ERROR_CHECK(gpio_set_direction(GNSS_RX, GPIO_MODE_INPUT));
    gpio_set_level(GNSS_RESET_N, 1);
    vTaskDelay(pdMS_TO_TICKS(1000));

    bool physical_pass = false;
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    ESP_ERROR_CHECK(uart_set_line_inverse(UART_NUM_1, inverted ? UART_SIGNAL_RXD_INV : 0));

    gpio_config_t reset_config = {};
    reset_config.pin_bit_mask = 1ULL << GNSS_RESET_N;
    reset_config.mode = GPIO_MODE_INPUT_OUTPUT_OD;
    ESP_ERROR_CHECK(gpio_config(&reset_config));
    gpio_set_level(GNSS_RESET_N, 0);
    vTaskDelay(pdMS_TO_TICKS(100));
    gpio_set_level(GNSS_RESET_N, 1);
    vTaskDelay(pdMS_TO_TICKS(1000));

    uint8_t discard[256];
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void characterize_gnss_pins()
{
    gpio_config_t reset = {};
    reset.pin_bit_mask = 1ULL << GNSS_RESET_N;
    reset.mode = GPIO_MODE_INPUT_OUTPUT_OD;
    ESP_ERROR_CHECK(gpio_config(&reset));
    gpio_set_level(GNSS_RESET_N, 1);
    vTaskDelay(pdMS_TO_TICKS(50));

    ESP_ERROR_CHECK(gpio_set_direction(GNSS_RX, GPIO_MODE_INPUT));
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    vTaskDelay(pdMS_TO_TICKS(20));
    int run_pulldown = majority_gpio_level(GNSS_RX);

    gpio_set_level(GNSS_RESET_N, 0);
    vTaskDelay(pdMS_TO_TICKS(100));
    ESP_ERROR_CHECK(gpio_set_pull_mode(GNSS_RX, GPIO_PULLUP_ONLY));
    vTaskDelay(pdMS_TO_TICKS(20));
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    ESP_ERROR_CHECK(gpio_set_pull_mode(GNSS_RX, GPIO_PULLDOWN_ONLY));
    vTaskDelay(pdMS_TO_TICKS(20));
    int reset_pulldown = majority_gpio_level(GNSS_RX);
    gpio_set_level(GNSS_RESET_N, 1);
    ESP_ERROR_CHECK(gpio_set_pull_mode(GNSS_RX, GPIO_PULLUP_ONLY));
    ESP_LOGI(TAG, "GNSS TXD drive test: run pull-up=%d pull-down=%d; reset pull-up=%d pull-down=%d",
             run_pullup, run_pulldown, reset_pullup, reset_pulldown);
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
    // Verify the board pull-up, then issue a clean active-low hardware reset.
    gpio_config_t reset_config = {};
    reset_config.pin_bit_mask = 1ULL << GNSS_RESET_N;
    reset_config.mode = GPIO_MODE_INPUT_OUTPUT_OD;
    ESP_ERROR_CHECK(gpio_config(&reset_config));
    gpio_set_level(GNSS_RESET_N, 1);
    vTaskDelay(pdMS_TO_TICKS(20));
    ESP_LOGI(TAG, "GNSS electrical levels before reset: RESET_N=%d TXD/ESP_RX=%d",
             gpio_get_level(GNSS_RESET_N), gpio_get_level(GNSS_RX));
    gpio_set_level(GNSS_RESET_N, 0);
    vTaskDelay(pdMS_TO_TICKS(100));
    ESP_LOGI(TAG, "GNSS electrical levels during reset: RESET_N=%d TXD/ESP_RX=%d (TIMEPULSE forced High)",
             gpio_get_level(GNSS_RESET_N), gpio_get_level(GNSS_RX));
    gpio_set_level(GNSS_RESET_N, 1);
    esp_rom_delay_us(2000);
    ESP_ERROR_CHECK(gpio_set_direction(GNSS_TIMEPULSE, GPIO_MODE_INPUT));
    ESP_ERROR_CHECK(gpio_set_pull_mode(GNSS_TIMEPULSE, GPIO_PULLUP_ONLY));
    vTaskDelay(pdMS_TO_TICKS(998));
    ESP_LOGI(TAG, "GNSS electrical levels after reset: RESET_N=%d TXD/ESP_RX=%d",
             gpio_get_level(GNSS_RESET_N), gpio_get_level(GNSS_RX));

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    uint8_t response[2048];
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bool test_can2()
{
    gpio_config_t reset = {};
    reset.pin_bit_mask = 1ULL << CAN2_RESET; reset.mode = GPIO_MODE_OUTPUT;
    ESP_ERROR_CHECK(gpio_config(&reset));
    gpio_set_level(CAN2_RESET, 0); vTaskDelay(pdMS_TO_TICKS(10));
    gpio_set_level(CAN2_RESET, 1); vTaskDelay(pdMS_TO_TICKS(20));

    spi_bus_config_t bus = {};
    bus.mosi_io_num = CAN2_MOSI; bus.miso_io_num = CAN2_MISO; bus.sclk_io_num = CAN2_SCK;
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
    spi_device_interface_config_t device_config = {};
    device_config.mode = 0; device_config.clock_speed_hz = 1000000;
    device_config.spics_io_num = CAN2_CS; device_config.queue_size = 1;
    spi_device_handle_t device = nullptr;
    error = spi_bus_add_device(SPI2_HOST, &device_config, &device);
    if (error != ESP_OK) { ESP_LOGE(TAG, "CAN2 SPI device FAIL: %s", esp_err_to_name(error)); spi_bus_free(SPI2_HOST); return false; }
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    ESP_LOGI(TAG, "CAN external test: J4(CAN2) <-> J5(CAN1), 500 kbit/s, 32 frames each direction");

    gpio_config_t reset = {};
    reset.pin_bit_mask = 1ULL << CAN2_RESET;
    reset.mode = GPIO_MODE_OUTPUT;
    ESP_ERROR_CHECK(gpio_config(&reset));
    gpio_set_level(CAN2_RESET, 0);
    vTaskDelay(pdMS_TO_TICKS(10));
    gpio_set_level(CAN2_RESET, 1);
    vTaskDelay(pdMS_TO_TICKS(20));

    spi_bus_config_t bus = {};
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    ESP_ERROR_CHECK(temperature_sensor_install(&temp_config, &temp_sensor));
    ESP_ERROR_CHECK(temperature_sensor_enable(temp_sensor));
    gpio_config_t inputs = {};
    inputs.pin_bit_mask = (1ULL << OTG_VBUS_SENSE) | (1ULL << OTG_OC_N) | (1ULL << OTG_ROLE);
    inputs.mode = GPIO_MODE_INPUT;
    ESP_ERROR_CHECK(gpio_config(&inputs));
    xTaskCreatePinnedToCore(stress_task, "stress0", 3072, reinterpret_cast<void *>(0), 1, nullptr, 0);
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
